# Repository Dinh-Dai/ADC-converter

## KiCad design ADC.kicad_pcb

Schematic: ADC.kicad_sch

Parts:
C1, C2, C3, C4: 47uF; C_Radial_D8.0mm_H7.0mm_P3.50mm
C7, C10: 22uF; C_0805_2012Metric
C9, C13, C20, C35, C39, C40: 10uF; C_0603_1608Metric
C12, C42: 10p; C_0402_1005Metric
C14, C15, C16, C28, C30: 100n; C_0402_1005Metric
C17, C21, C22, C31, C34, C38, C41: 100nF; C_0402_1005Metric
C18, C19: 18pF; C_0402_1005Metric
C23: 47uF; C_0805_2012Metric
C24, C25, C26, C27, C33: 100pF; C_0402_1005Metric
C29, C32: 10n; C_0402_1005Metric
C36, C37: 1n; C_0402_1005Metric
C43: 680uF; C_Radial_D8.0mm_H11.5mm_P3.50mm
C44: 220uF; C_Radial_D8.0mm_H11.5mm_P3.50mm
D1, D3: D_Schottky; D_0805_2012Metric
D2: LED; LED_0603_1608Metric
D4, D5: ZPDxx; D_DO-35_SOD27_P7.62mm_Horizontal
D6, D16, D17: SMDJ24CAH; DIOM6859X262N; PARTREV R2102
D7, D8, D9, D10, D11, D12, D13, D14, D15, D19, D21, D23: SMBJ15CA; DIOM4336X265N; PARTREV I2102
F1: Polyfuse; Fuse_1812_4532Metric
FB1, FB2: FerriteBead; L_0603_1608Metric
H1, H2, H3, H4: MountingHole; MountingHole_2.1mm
J1: Conn_01x03_Pin; PinHeader_1x03_P2.54mm_Vertical
J2: Screw_Terminal_01x02; TerminalBlock_Phoenix_MKDS-1,5-2_1x02_P5.00mm_Horizontal
J3: Screw_Terminal_01x09; TerminalBlock_Phoenix_MPT-0,5-9-2.54_1x09_P2.54mm_Horizontal
L1: 33uH; L_0603_1608Metric
L2: 100uH; L_0603_1608Metric
PS1: R12P212D; CONV_R12P212D; PARTREV 6
R1, R31, R37, R43, R55, R56, R57, R58, R75, R78: 2k; R_0402_1005Metric
R2, R25, R32, R38, R44, R59, R62, R65, R68, R76, R77: 1k; R_0402_1005Metric
R3, R29, R35, R41, R47, R48, R49, R50: 190; R_0402_1005Metric
R4, R5, R6, R7, R8, R9, R10, R12: 300; R_0402_1005Metric
R11, R13: 49.9; R_0402_1005Metric
R14, R15, R16: 100; R_0402_1005Metric
R17: 100K; R_0402_1005Metric
R18, R20: 4,7k; R_0402_1005Metric
R19: 120; R_0402_1005Metric
R21, R22: 10; R_0402_1005Metric
R23, R24: 10k; R_0402_1005Metric
R26, R27, R33, R34, R39, R40, R45, R46, R60, R61, R63, R64, R66, R67, R69, R70: 500; R_0402_1005Metric
R28, R30, R36, R42, R51, R52, R53, R54: 200; R_0402_1005Metric
R71, R72, R73, R74, R79, R80, R81, R82, R83, R84, R85, R86, R87, R88, R89, R90: 3k; R_0402_1005Metric
RV1: Varistor; RV_Disc_D7mm_W4.5mm_P5mm
SW1: SW_SPDT; SW_SPDT_PCM12
U1: ADS1256IDBR; SOP65P780X200-28N; DigiKey_Part_Number 296-25898-2-ND
U2: MCU-STM32F407VET6_LQFP100_; LQFP100-0.5-13.8X13.8MM; MPN STM32F407VET6
U3: ADM2483xRW; SOIC-16W_7.5x10.3mm_P1.27mm
U4: LM2596S-5; TO170P1524X483-6N
U5: DCP010505BP; DIP254P762X533-7P; MPN DCP010505BP
U6, U29, U30, U31: TLV1704AIPWR; SOP65P640X120-14N
U7, U13, U15, U17, U24, U25, U26, U27: OPA211ID; SOIC127P599X175-8N
U8: AMS1117-3.3; SOT-223-3_TabPin2
U9, U11, U14, U16, U20, U21, U22, U23: ADG5412FBCPZ-RL7; QFN65P400X400X80-17N
U10, U19: CD4514BM; SOIC127P1030X265-24N
U12: ADR421ARMZ; MSOP-8_3x3mm_P0.65mm
U18, U32: CD4072BM; SOIC127P600X175-14N
U28: CD4043BPWR; SOP65P640X120-16N
Y1: 8MHz; Crystal_HC49-4H_Vertical
Y2: ABM3B-25.000MHZ-D2Y-T; XTAL_ABM3B-25.000MHZ-D2Y-T; PARTREV 08.25.15

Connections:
+3.3V: C7.1, C13.1, C14.2, C15.2, C16.2, C17.1, C28.2, C29.2, C37.1, C38.1, C39.1, FB1.2, R2.1, R17.2, R24.1, R71.1, R72.1, R73.1, R74.2, R79.2, R80.1, R81.1, R82.1, R83.2, R84.2, R85.1, R86.1, R87.1, R88.1, R89.1, R90.1, SW1.3 (C), U1.16 (DVDD), U2.6 (VBAT), U2.11 (VDD@1), U2.19 (VDD@2), U2.28 (VDD@3), U2.50 (VDD@4), U2.75 (VDD@5), U3.1 (VDD1), U3.7 (PV), U8.2 (VO), U10.24 (VDD), U18.14 (VDD), U19.24 (VDD), U28.5 (ENABLE), U28.16 (VDD), U32.14 (VDD)
+3.3VA: C32.1, C36.1, FB1.1, U2.22 (VDDA)
+4V: R75.2, R76.1, U6.4 (1IN-), U6.8 (3LN-), U29.4 (1IN-), U29.8 (3LN-), U30.4 (1IN-), U30.8 (3LN-), U31.4 (1IN-), U31.8 (3LN-)
+5V: C1.1, C20.1, C21.1, C44.1, FB2.2, L1.2, U4.4 (FB), U5.1 (VS), U8.3 (VI), U12.2 (VIN)
+5V_ISO: C4.1, C9.1, C10.1, C40.1, C41.1, R18.1, U3.16 (VDD2), U5.6 (+VOUT)
+12V: C2.1, PS1.7 (+VOUT), R75.1, U6.3 (V+), U7.7 (V+), U9.11 (VDD), U11.11 (VDD), U13.7 (V+), U14.11 (VDD), U15.7 (V+), U16.11 (VDD), U17.7 (V+), U20.11 (VDD), U21.11 (VDD), U22.11 (VDD), U23.11 (VDD), U24.7 (V+), U25.7 (V+), U26.7 (V+), U27.7 (V+), U29.3 (V+), U30.3 (V+), U31.3 (V+)
+12V_IN: F1.1, J2.2
-4V: R77.2, R78.1, U6.7 (2LN+), U6.11 (4IN+), U29.7 (2LN+), U29.11 (4IN+), U30.7 (2LN+), U30.11 (4IN+), U31.7 (2LN+), U31.11 (4IN+)
-12V: C3.1, PS1.5 (-VOUT), R78.2, U6.12 (V_), U7.4 (V-), U9.2 (VSS), U11.2 (VSS), U13.4 (V-), U14.2 (VSS), U15.4 (V-), U16.2 (VSS), U17.4 (V-), U20.2 (VSS), U21.2 (VSS), U22.2 (VSS), U23.2 (VSS), U24.4 (V-), U25.4 (V-), U26.4 (V-), U27.4 (V-), U29.12 (V_), U30.12 (V_), U31.12 (V_)
/1_IN1: U9.15 (IN1), U10.5 (S6)
/1_IN2: U9.14 (IN2), U10.4 (S7)
/1_IN3: U9.7 (IN3), U10.7 (S4)
/1_IN4: U9.6 (IN4), U10.6 (S5)
/2_IN1: U10.9 (S2), U11.15 (IN1)
/2_IN2: U10.8 (S3), U11.14 (IN2)
/2_IN4: U10.20 (S10), U11.6 (IN4)
/2_in3: U10.10 (S1), U11.7 (IN3)
/3_IN1: U10.11 (S0), U14.15 (IN1)
/3_IN2: U10.19 (S11), U14.14 (IN2)
/3_IN3: U10.17 (S9), U14.7 (IN3)
/3_IN4: U10.18 (S8), U14.6 (IN4)
/4_IN1: U10.15 (S15), U16.15 (IN1)
/4_IN2: U10.16 (S14), U16.14 (IN2)
/4_IN3: U10.13 (S13), U16.7 (IN3)
/4_IN4: U10.14 (S12), U16.6 (IN4)
/5_IN1: U19.5 (S6), U22.15 (IN1)
/5_IN2: U19.4 (S7), U22.14 (IN2)
/5_IN3: U19.7 (S4), U22.7 (IN3)
/5_IN4: U19.6 (S5), U22.6 (IN4)
/6_IN1: U19.9 (S2), U23.15 (IN1)
/6_IN2: U19.8 (S3), U23.14 (IN2)
/6_IN3: U19.11 (S0), U23.7 (IN3)
/6_IN4: U19.10 (S1), U23.6 (IN4)
/7_IN1: U19.14 (S12), U20.15 (IN1)
/7_IN2: U19.13 (S13), U20.14 (IN2)
/7_IN3: U19.16 (S14), U20.7 (IN3)
/7_IN4: U19.15 (S15), U20.6 (IN4)
/8_IN1: U19.18 (S8), U21.15 (IN1)
/8_IN2: U19.17 (S9), U21.14 (IN2)
/8_IN3: U19.20 (S10), U21.7 (IN3)
/8_IN4: U19.19 (S11), U21.6 (IN4)
/AIN0: C24.2, R4.1, U1.6 (AIN0)
/AIN1: C24.1, R5.1, U1.7 (AIN1)
/AIN2: C25.2, R6.1, U1.8 (AIN2)
/AIN3: C25.1, R7.1, U1.9 (AIN3)
/AIN4: C26.2, R8.1, U1.10 (AIN4)
/AIN5: C26.1, R9.1, U1.11 (AIN5)
/AIN6: C27.2, R10.1, U1.12 (AIN6)
/AIN7: C27.1, R12.1, U1.13 (AIN7)
/SW_BOOTO: R23.1, SW1.2 (B)
/VREFN: C23.2, C31.2, C33.2, R13.2, U1.3 (VREFN)
/VREFP: C23.1, C31.1, C33.1, R11.2, U1.4 (VREFP)
ADC1: R4.2, U6.5 (1IN+), U6.6 (2LN-), U9.1 (S1), U9.9 (S3), U9.12 (S2)
ADC2: R5.2, U6.9 (3LN+), U6.10 (4IN-), U11.1 (S1), U11.9 (S3), U11.12 (S2)
ADC3: R6.2, U14.1 (S1), U14.9 (S3), U14.12 (S2), U29.5 (1IN+), U29.6 (2LN-)
ADC4: R7.2, U16.1 (S1), U16.9 (S3), U16.12 (S2), U29.9 (3LN+), U29.10 (4IN-)
ADC5: R8.2, U22.1 (S1), U22.9 (S3), U22.12 (S2), U30.5 (1IN+), U30.6 (2LN-)
ADC6: R9.2, U23.1 (S1), U23.9 (S3), U23.12 (S2), U30.9 (3LN+), U30.10 (4IN-)
ADC7: R10.2, U20.1 (S1), U20.9 (S3), U20.12 (S2), U31.5 (1IN+), U31.6 (2LN-)
ADC8: R12.2, U21.1 (S1), U21.9 (S3), U21.12 (S2), U31.9 (3LN+), U31.10 (4IN-)
ADC_RESET: R17.1, U1.15 (~RESET), U2.86 (PD5)
CS: R16.2, U2.87 (PD6)
DECODER1_1: U2.57 (PD10), U10.2 (DATA1)
DECODER1_2: U2.58 (PD11), U10.3 (DATA2)
DECODER1_3: U2.59 (PD12), U10.21 (DATA3)
DECODER1_4: U2.60 (PD13), U10.22 (DATA4)
DECODER2_1: U2.63 (PC6), U19.2 (DATA1)
DECODER2_2: U2.64 (PC7), U19.3 (DATA2)
DECODER2_3: U2.65 (PC8), U19.21 (DATA3)
DECODER2_4: U2.66 (PC9), U19.22 (DATA4)
DE/RE: R24.2, U2.46 (PE15), U3.4 (~RE), U3.5 (DE)
DRDY: U1.21 (~DRDY), U2.88 (PD7)
GND: C1.2, C2.2, C3.2, C7.2, C12.2, C13.2, C14.1, C15.1, C16.1, C17.2, C18.2, C19.2, C20.2, C21.2, C28.1, C29.1, C30.2, C32.2, C34.2, C35.2, C36.2, C37.2, C38.2, C39.2, C42.2, C43.2, C44.2, D1.2 (A), D2.1 (K), D3.2 (A), D7.2, D8.2, D9.2, D10.2, D11.2, D12.2, D13.2, D15.2, D17.2, J2.1, J3.1, PS1.2 (-VIN), PS1.6 (COM), R27.1, R34.1, R40.1, R46.1, R61.1, R64.1, R67.1, R70.1, R76.2, R77.1, SW1.1 (A), U1.2 (AGND), U1.5 (AINCOM), U1.17 (DGND), U2.10 (VSS@1), U2.20 (VSSA), U2.27 (VSS@2), U2.74 (VSS@3), U2.99 (VSS@4), U2.100 (VDD@6), U3.2 (GND1), U3.8 (GND1), U4.3 (GND), U4.5 (~ON/OFF), U5.2 (0V_2), U8.1 (GND), U9.3 (GND), U9.4 (S4), U9.17 (EP), U10.12 (VSS), U11.3 (GND), U11.4 (S4), U11.17 (EP), U12.4 (GND), U14.3 (GND), U14.4 (S4), U14.17 (EP), U16.3 (GND), U16.4 (S4), U16.17 (EP), U18.7 (VSS), U19.12 (VSS), U20.3 (GND), U20.4 (S4), U20.17 (EP), U21.3 (GND), U21.4 (S4), U21.17 (EP), U22.3 (GND), U22.4 (S4), U22.17 (EP), U23.3 (GND), U23.4 (S4), U23.17 (EP), U28.8 (VSS), U32.7 (VSS), Y2.2 (GND), Y2.4 (GND)
GND_ISO: C4.2, C9.2, C10.2, C40.2, C41.2, D4.2 (A), D5.2 (A), D6.2, D16.2, J1.1, R20.2, U3.9 (GND2), U3.15 (GND2), U5.5 (0V)
LOCK1: U10.23 (INHIBIT), U28.2 (Q1)
LOCK2: U10.1 (STROBE), U28.9 (Q2)
LOCK3: U19.23 (INHIBIT), U28.10 (Q3)
LOCK4: U19.1 (STROBE), U28.1 (Q4)
unnamed: C22.2, R13.1
unnamed: D1.1 (K), D17.1, F1.2, L2.1
unnamed: D2.2 (A), R2.2
unnamed: D3.1 (K), L1.1, U4.2 (OUT)
unnamed: D4.1 (K), D16.1, J1.3, R21.2
unnamed: D5.1 (K), D6.1, J1.2, R22.2
unnamed: C43.1, L2.2, PS1.1 (+VIN), U4.1 (VIN)
unnamed: C34.1, C35.1, FB2.1, U1.1 (AVDD), U1.14 (~SYNC,_~PDWN)
unnamed: R15.1, U1.23 (DIN)
unnamed: R14.1, U1.24 (SCLK)
unnamed: C18.1, U1.19 (XTAL1/CLKIN), Y1.2
unnamed: C19.1, U1.18 (XTAL2), Y1.1
unnamed: R16.1, U1.20 (~CS)
unnamed: R23.2, U2.94 (BOOT0)
unnamed: C30.1, U2.14 (NRST)
unnamed: C12.1, U2.12 (PH0), Y2.1
unnamed: C42.1, U2.13 (PH1), Y2.3
unnamed: R18.2, R19.1, R21.1, RV1.1, U3.12 (A)
unnamed: R19.2, R20.1, R22.1, RV1.2, U3.13 (B)
unnamed: R1.1, R3.1, U7.2 (-IN)
unnamed: R1.2, R25.2, R28.1, U7.6 (OUT)
unnamed: R26.1, R27.2, U9.16 (D1)
unnamed: R25.1, R26.2, U9.13 (D2)
unnamed: R28.2, U9.8 (D3)
unnamed: R3.2, U9.5 (D4)
unnamed: R33.1, R34.2, U11.16 (D1)
unnamed: R32.1, R33.2, U11.13 (D2)
unnamed: R30.2, U11.8 (D3)
unnamed: R29.2, U11.5 (D4)
unnamed: C22.1, R11.1, U12.6 (OUT)
unnamed: R29.1, R31.1, U13.2 (-IN)
unnamed: R30.1, R31.2, R32.2, U13.6 (OUT)
unnamed: R39.1, R40.2, U14.16 (D1)
unnamed: R38.1, R39.2, U14.13 (D2)
unnamed: R36.2, U14.8 (D3)
unnamed: R35.2, U14.5 (D4)
unnamed: R35.1, R37.1, U15.2 (-IN)
unnamed: R36.1, R37.2, R38.2, U15.6 (OUT)
unnamed: R45.1, R46.2, U16.16 (D1)
unnamed: R44.1, R45.2, U16.13 (D2)
unnamed: R42.2, U16.8 (D3)
unnamed: R41.2, U16.5 (D4)
unnamed: R41.1, R43.1, U17.2 (-IN)
unnamed: R42.1, R43.2, R44.2, U17.6 (OUT)
unnamed: R74.1, U6.13 (40UT), U18.2 (A)
unnamed: R73.2, U6.14 (30UT), U18.3 (B)
unnamed: R72.2, U6.1 (20UT), U18.4 (C)
unnamed: R71.2, U6.2 (10UT), U18.5 (D)
unnamed: R79.1, U18.9 (E), U29.13 (40UT)
unnamed: R80.2, U18.10 (F), U29.14 (30UT)
unnamed: R81.2, U18.11 (G), U29.1 (20UT)
unnamed: R82.2, U18.12 (H), U29.2 (10UT)
unnamed: U18.1 (J=A+B+C+D), U28.4 (S1)
unnamed: U18.13 (K=E+F+G+H), U28.6 (S2)
unnamed: R60.1, R61.2, U20.16 (D1)
unnamed: R59.1, R60.2, U20.13 (D2)
unnamed: R51.2, U20.8 (D3)
unnamed: R47.2, U20.5 (D4)
unnamed: R63.1, R64.2, U21.16 (D1)
unnamed: R62.1, R63.2, U21.13 (D2)
unnamed: R52.2, U21.8 (D3)
unnamed: R48.2, U21.5 (D4)
unnamed: R66.1, R67.2, U22.16 (D1)
unnamed: R65.1, R66.2, U22.13 (D2)
unnamed: R53.2, U22.8 (D3)
unnamed: R49.2, U22.5 (D4)
unnamed: R69.1, R70.2, U23.16 (D1)
unnamed: R68.1, R69.2, U23.13 (D2)
unnamed: R54.2, U23.8 (D3)
unnamed: R50.2, U23.5 (D4)
unnamed: R47.1, R55.1, U24.2 (-IN)
unnamed: R51.1, R55.2, R59.2, U24.6 (OUT)
unnamed: R48.1, R56.1, U25.2 (-IN)
unnamed: R52.1, R56.2, R62.2, U25.6 (OUT)
unnamed: R49.1, R57.1, U26.2 (-IN)
unnamed: R53.1, R57.2, R65.2, U26.6 (OUT)
unnamed: R50.1, R58.1, U27.2 (-IN)
unnamed: R54.1, R58.2, R68.2, U27.6 (OUT)
unnamed: U28.12 (S3), U32.1 (J=A+B+C+D)
unnamed: U28.14 (S4), U32.13 (K=E+F+G+H)
unnamed: R89.2, U30.2 (10UT), U32.5 (D)
unnamed: R87.2, U30.1 (20UT), U32.4 (C)
unnamed: R85.2, U30.14 (30UT), U32.3 (B)
unnamed: R83.1, U30.13 (40UT), U32.2 (A)
unnamed: R90.2, U31.2 (10UT), U32.12 (H)
unnamed: R88.2, U31.1 (20UT), U32.11 (G)
unnamed: R86.2, U31.14 (30UT), U32.10 (F)
unnamed: R84.1, U31.13 (40UT), U32.9 (E)
RESET: U2.62 (PD15), U28.3 (R1), U28.7 (R2), U28.11 (R3), U28.15 (R4)
SPI3_MISO: U1.22 (DOUT), U2.90 (PB4)
SPI3_MOSI: R15.2, U2.91 (PB5)
SPI3_SCK: R14.2, U2.89 (PB3)
UART RX: U2.48 (PB11), U3.3 (RxD)
UART TX: U2.47 (PB10), U3.6 (TxD)
VinN1: D12.1, D23.2, J3.3, U13.3 (+IN)
VinN2: D10.1, D21.2, J3.5, U17.3 (+IN)
VinN3: D8.1, D19.2, J3.7, U27.3 (+IN)
VinN4: D14.2, D15.1, J3.9, U25.3 (+IN)
VinP1: D13.1, D23.1, J3.2, U7.3 (+IN)
VinP2: D11.1, D21.1, J3.4, U15.3 (+IN)
VinP3: D9.1, D19.1, J3.6, U26.3 (+IN)
VinP4: D7.1, D14.1, J3.8, U24.3 (+IN)

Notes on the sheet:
ADM2483xRW
STM32F407
Isolated DC/DC converter
ADS1256IDBR
1x 100nF per VDD pin
Power Supply 5v and +-12V
Power Supply 3.3V

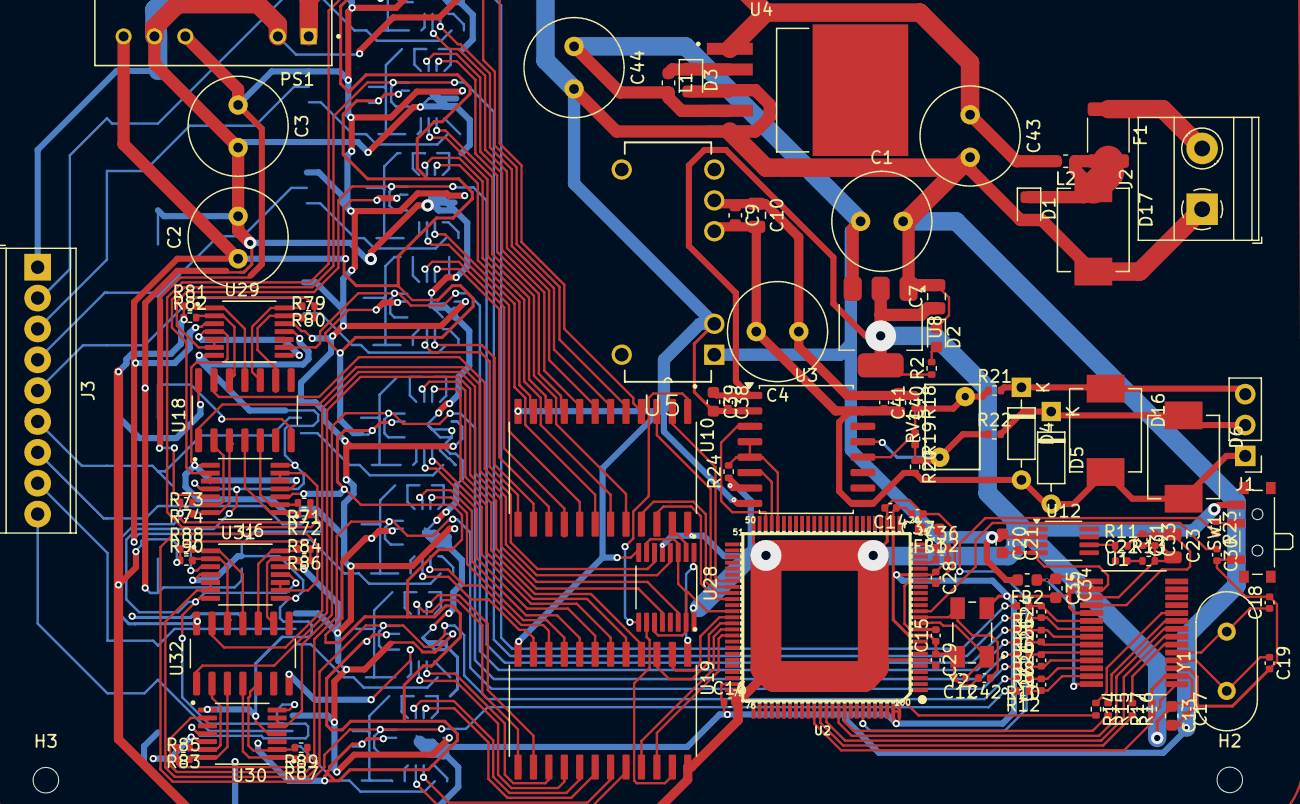
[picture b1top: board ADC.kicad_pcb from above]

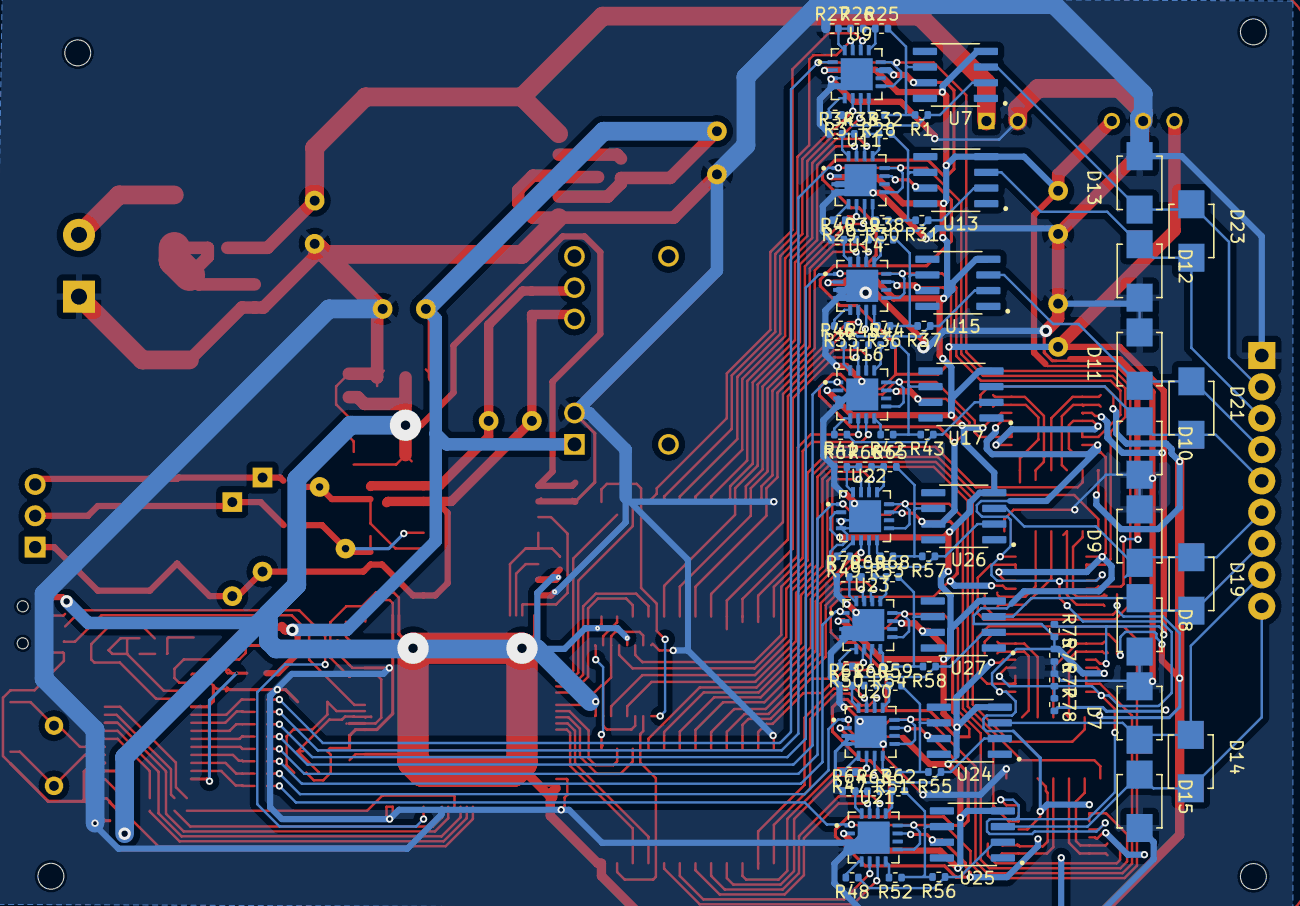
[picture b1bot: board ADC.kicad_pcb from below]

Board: 2 copper layers, 199 parts (80 on the bottom side), 180 nets.

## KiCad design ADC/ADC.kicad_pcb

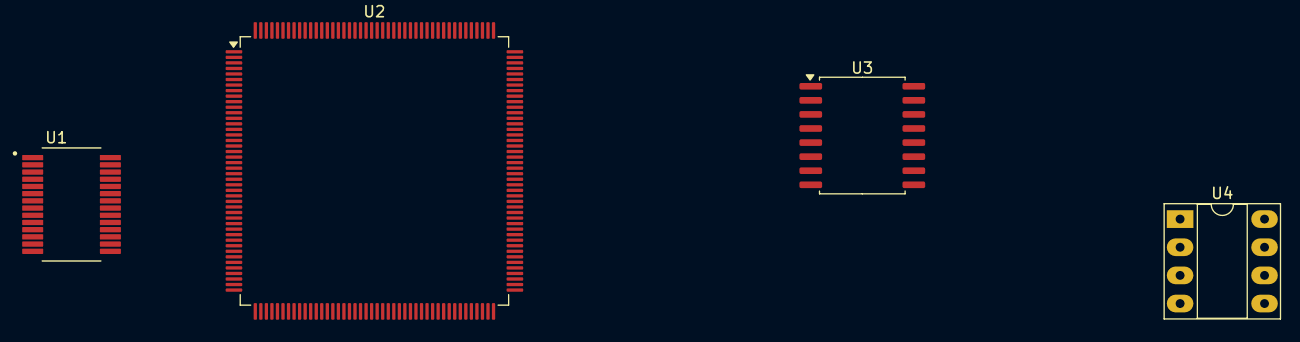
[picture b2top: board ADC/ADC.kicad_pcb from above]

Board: 2 copper layers, 4 parts (0 on the bottom side), 3 nets, no tracks yet.

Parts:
U1: ADS1256IDBR; SOP65P780X200-28N
U2: STM32F407IETx; LQFP-176_24x24mm_P0.5mm
U3: ADM2483xRW; SOIC-16W_7.5x10.3mm_P1.27mm
U4: MAX485E; DIP-8_W7.62mm_Socket_LongPads

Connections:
unnamed: U2.14 (VSS), U2.22 (VSS), U2.61 (VSS), U2.71 (VSS), U2.90 (VSS), U2.102 (VSS), U2.113 (VSS), U2.126 (VSS), U2.135 (VSS), U2.148 (VSS), U2.158 (VSS)
unnamed: U3.2 (GND1), U3.8 (GND1)
unnamed: U3.9 (GND2), U3.15 (GND2)

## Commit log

2024-12-10 xóa hello
2024-12-10 add kháng sét cho ADM
2024-12-11 nối chân est32
2024-12-11 Add a file
2024-12-11 xoa file thua
2024-12-11 fix bug
2024-12-11 thêm thạch anh
2024-12-11 Vẽ LM, Thêm cổng cho nguồn và analog
2024-12-11 Sửa tụ
2024-12-11 Bảo vệ nguồn
2024-12-12 Thêm GND
2024-12-12 Thêm linh kiện
2024-12-12 Thêm 3 linh kiện
2024-12-12 ADD ADG
2024-12-12 Add digital
2024-12-12 thêm tiền sử lí ADC
2024-12-13 Add linh kiên
2024-12-13 ok roài
2024-12-13 Them bao ve
2024-12-13 Add TLV
2024-12-13 add CD
2024-12-13 Them Cd
2024-12-13 hoàn thành bảo vệ ADC
2024-12-13 Add SMDJ
2024-12-13 hoàn thiện
2024-12-18 phước mai fix các lỗi đi
2024-12-19 Add footprint, 3d
2024-12-20 add 3d
2024-12-20 thêm 3D MKDS và MPT
2024-12-20 add file đg dẫn
2024-12-20 thêm 3d all
2024-12-20 chia khu linh kiện PCB
2024-12-21 xong bộ bám điện áp, khuếch đại
2024-12-21 đã tìm được đường đi cho nhưng dây phức tạp
2024-12-22 đã xong các dây dữ liệu
2024-12-22 gần như xong
2024-12-24 Đi dây những linh kiện còn lại rồi tăng kích thước dây đi
2024-12-24 phóng to dây nguồn và gnd
2024-12-24 gần xong
2024-12-24 sửa lại dây kích cỡ cũ
2024-12-25 tăng kích cỡ dây
2024-12-25 xóa cái phước làm
